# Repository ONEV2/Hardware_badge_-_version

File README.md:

# Hardware_badge_-_version
This repo contains the prototype of hardware badge currently in development by me

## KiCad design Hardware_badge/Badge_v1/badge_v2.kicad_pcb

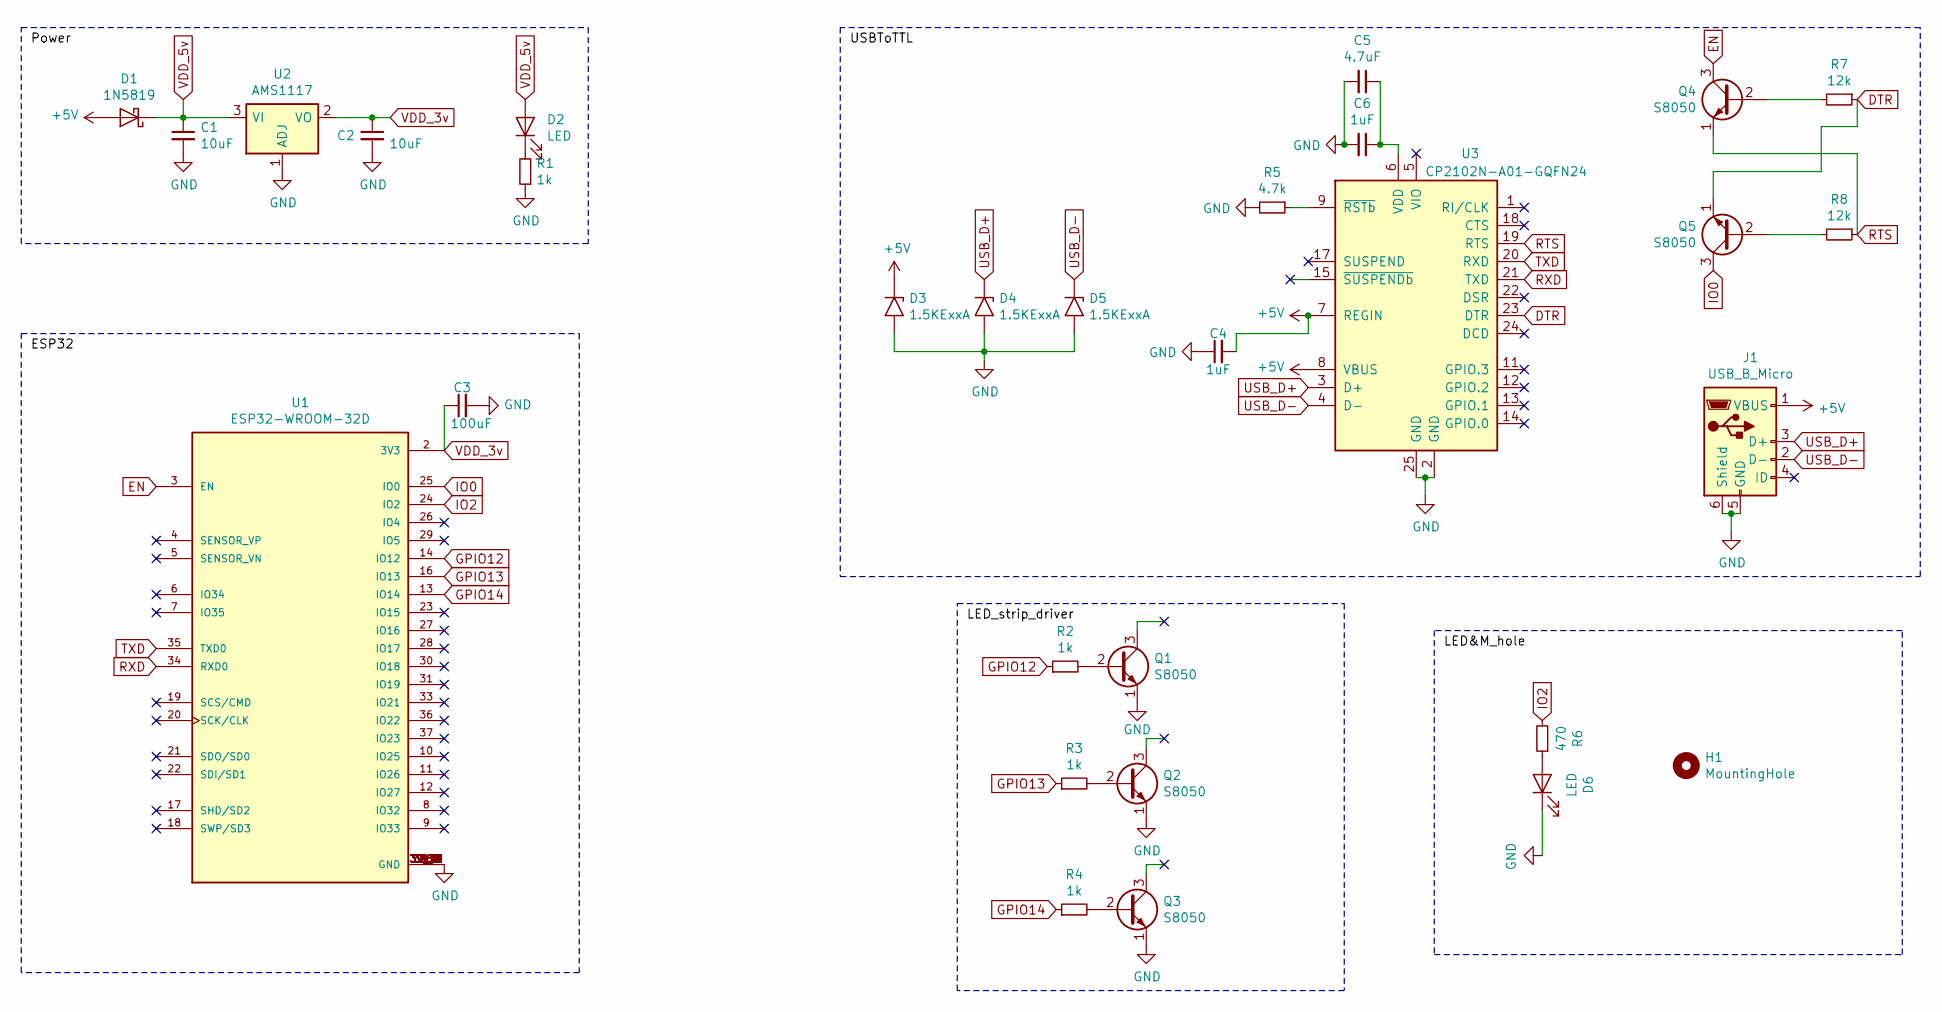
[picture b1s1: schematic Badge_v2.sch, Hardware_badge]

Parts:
C1, C2: 10uF; C_0402_1005Metric
C3: 100uF; C_0402_1005Metric
C4, C6: 1uF; C_0402_1005Metric
C5: 4.7uF; C_0402_1005Metric
D1: 1N5819; D_0402_1005Metric
D2, D6: LED; LED_0402_1005Metric
D3, D4, D5: 1.5KExxA; D_0402_1005Metric
H1: MountingHole; middle_circle
J1: USB_B_Micro; USB_Micro-B_GCT_USB3076-30-A
Q1, Q2, Q3, Q4, Q5: S8050; SOT95P240X120-3N
R1, R2, R3, R4: 1k; R_01005_0402Metric
R5: 4.7k; R_01005_0402Metric
R6: 470; R_01005_0402Metric
R7, R8: 12k; R_01005_0402Metric
U1: ESP32-WROOM-32D; MODULE_ESP32-WROOM-32D; PARTREV 1.9
U2: AMS1117; SOT-223-3_TabPin2
U3: CP2102N-A01-GQFN24; QFN-24-1EP_4x4mm_P0.5mm_EP2.6x2.6mm

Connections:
+5V: C4.2, D1.2 (A), D3.1 (A1), J1.1 (VBUS), U3.7 (REGIN), U3.8 (VBUS)
DTR: Q5.1 (E), R7.1, U3.23 (DTR)
EN: Q4.3 (C), U1.3 (EN)
GND: C1.2, C2.2, C3.2, C4.1, C5.2, C6.2, D3.2 (A2), D4.2 (A2), D5.2 (A2), D6.1 (K), J1.5 (GND), J1.6 (Shield), Q1.1 (E), Q2.1 (E), Q3.1 (E), R1.1, R5.2, U1.1 (GND), U1.15 (GND), U1.38 (GND), U1.39_1 (GND), U1.39_2 (GND), U1.39_3 (GND), U1.39_4 (GND), U1.39_5 (GND), U1.39_6 (GND), U1.39_7 (GND), U1.39_8 (GND), U1.39_9 (GND), U1.39_10 (GND), U1.39_11 (GND), U1.39_12 (GND), U1.39_13 (GND), U1.39_14 (GND), U1.39_15 (GND), U1.39_16 (GND), U1.39_17 (GND), U1.39_18 (GND), U1.39_19 (GND), U1.39_20 (GND), U1.39_21 (GND), U2.1 (ADJ), U3.2 (GND), U3.25 (GND)
GPIO12: R2.1, U1.14 (IO12)
GPIO13: R3.1, U1.16 (IO13)
GPIO14: R4.1, U1.13 (IO14)
IO0: Q5.3 (C), U1.25 (IO0)
IO2: R6.2, U1.24 (IO2)
unnamed: C5.1, C6.1, U3.6 (VDD)
unnamed: D2.1 (K), R1.2
unnamed: D6.2 (A), R6.1
unnamed: Q1.2 (B), R2.2
unnamed: Q2.2 (B), R3.2
unnamed: Q3.2 (B), R4.2
unnamed: Q4.2 (B), R7.2
unnamed: Q5.2 (B), R8.2
unnamed: R5.1, U3.9 (~RSTb)
RTS: Q4.1 (E), R8.1, U3.19 (RTS)
RXD: U1.34 (RXD0), U3.21 (TXD)
TXD: U1.35 (TXD0), U3.20 (RXD)
USB_D+: D4.1 (A1), J1.3 (D+), U3.3 (D+)
USB_D-: D5.1 (A1), J1.2 (D-), U3.4 (D-)
VDD_3v: C2.1, C3.1, U1.2 (3V3), U2.2 (VO)
VDD_5v: C1.1, D1.1 (K), D2.2 (A), U2.3 (VI)

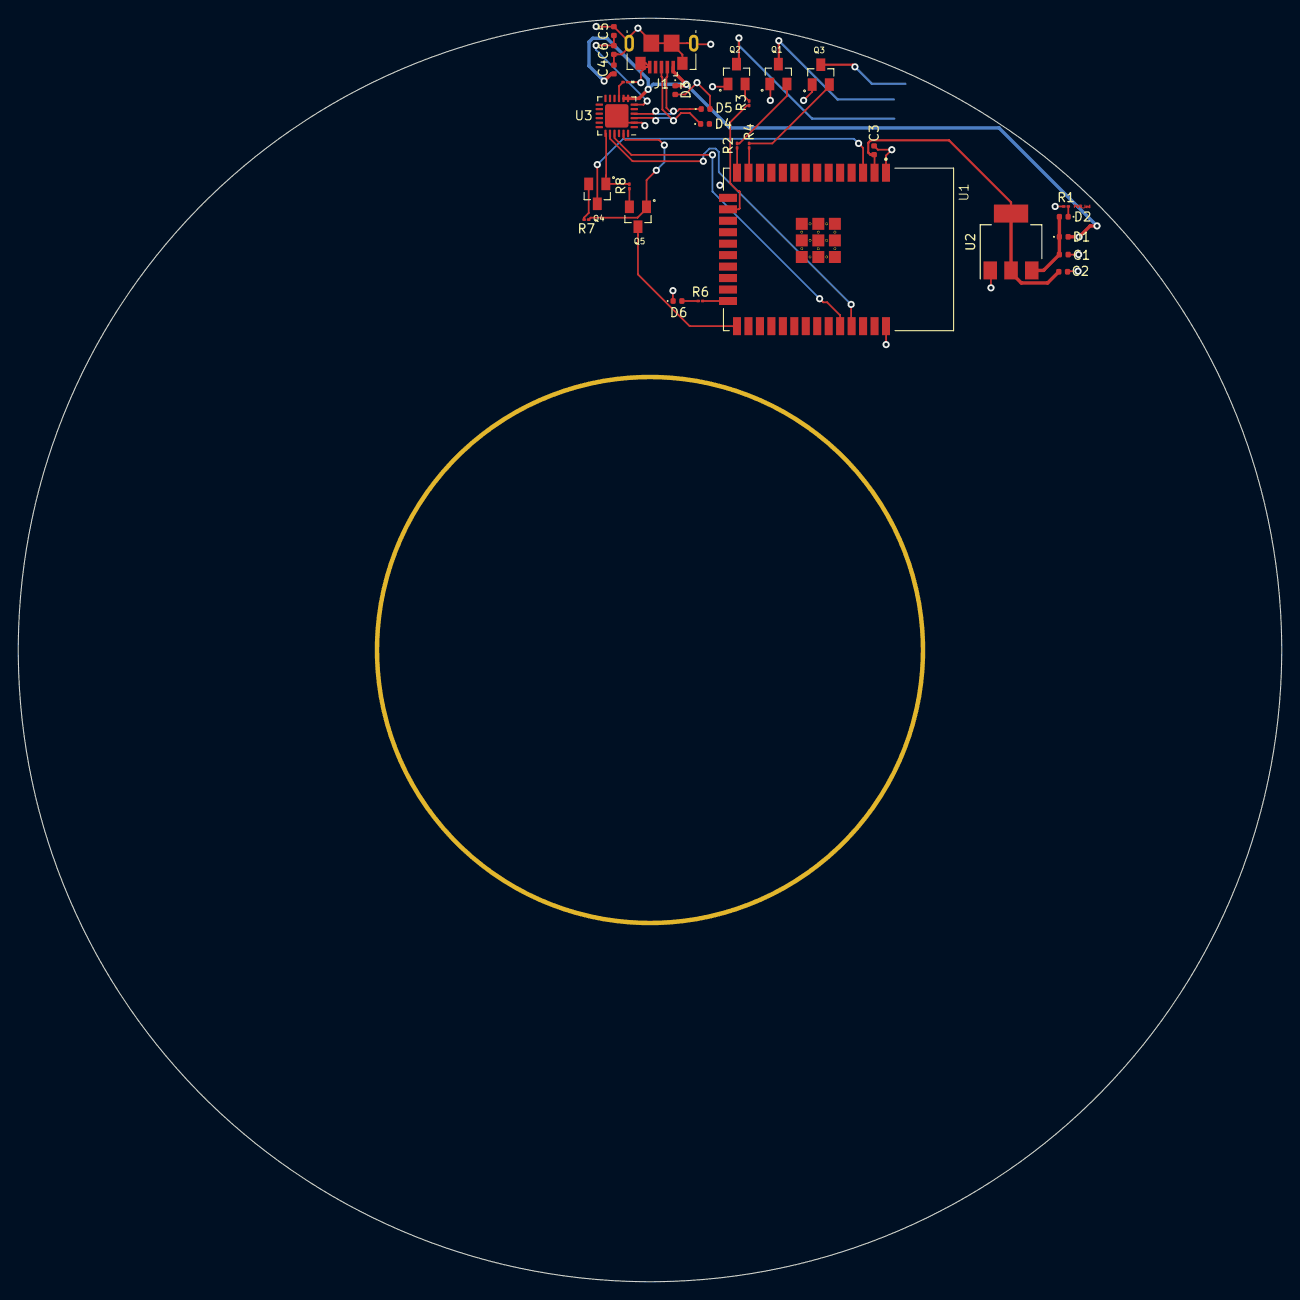
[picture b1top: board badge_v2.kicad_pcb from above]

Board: 2 copper layers, 140.0 x 140.0 mm, 30 parts (0 on the bottom side), 25 nets.

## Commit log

2022-07-13 Add: badge files
2022-07-13 Add: Image files for readme
